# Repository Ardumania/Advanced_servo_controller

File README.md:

# Advanced_servo_controller
Based on ATtiny85 and PJON bus

In the last years I have worked in several projects related with education and robotics 
and I have found several problems, if you work with only one microcontroller you are very 
limited about the number of servos you can drive, you need a separate controller to 
drive until 32 servos, but it’s still possible. What about sensors? if you are planning 
to build an hexapod and mount two distance sensor for each leg It’s practically impossible.

There are systems for robotics that consist in smart servos connected by a RS-485 bus 
(Dynamixel or Ubtech), but in these systems is not possible to implement sensors on the 
same bus. And other problem is that those systems use a closed protocol and developers 
can’t implement their own sensors or actuators.

For several time I was thinking in an alternative system for implement sensors and actuators 
in a same communication bus and, of course, do it open allowing developers and enthusiast to 
design their own modules and share them. Initially thought in I2C bus be cause is well 
documented and easy to use but need 4 wires and there are no standard cable to use, this 
is an inconvenient.

In May 2015 I was talking in Valencia with my mentor and friend David Cuartielles about 
this project and he made me a suggestion: the PJON bus developed by an italian guy 
(Giovanni Blu), it’s one wire, addressable, fully bi-directional and open. That was 
instant love and this project could start.
PJON project can be found here: https://github.com/gioblu/PJON

The main goal of this project is to build a net of modules that can talk to each others
and with the main controller by only a one wire. Just think about it: one wire for data, 
one wire for GND and another wire for VCC, you can have a net of actuators and sensors 
just connected by standard servo wires… and can be connected up to 256 devices.

The first prototype is a servo module, actually called Advanced Servo Controller, and 
is in a very early state of development but it will work for sure be cause the concept 
is very simple: a small pcb with an ATtiny85 that communicates with a main controller 
(Arduino, of course) via a PJON bus, this ATtiny receives commands and generates the 
servo control signals. Commands can be like AT commands, e.g. “GT1500,2000”, this is 
Go To position 1500 in 2000 milliseconds, position is the servo control signal duty 
cycle in microseconds and final time is the time in which must reach that position 
from its actual position… simple. Each module has a current sensor a can send readings 
to the main controller as responses to a specific requests… and more capabilities can 
be implemented in the module firmware in the future.

In the future can be implemented more types of modules with sensors, e.g. distance sensors, 
which are very interesting in robotics.

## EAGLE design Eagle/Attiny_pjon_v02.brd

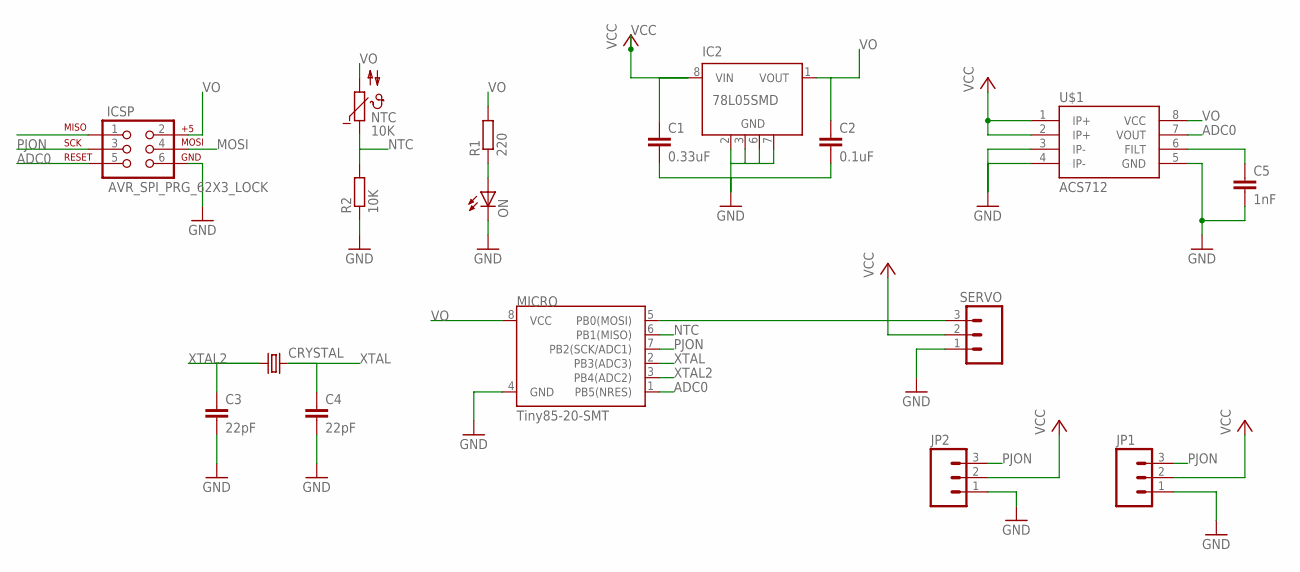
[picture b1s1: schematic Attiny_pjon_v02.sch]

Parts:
C1: 0.33uF; C1206
C2: 0.1uF; C1206
C3, C4: 22pF; C1206
C5: 1nF; C1206
CRYSTAL: CRYSTALSMD; HC49UP
IC2: 78L05SMD; SO08
ICSP: AVR_SPI_PRG_62X3_LOCK; 2X3_LOCK
JP1, JP2: M03PTH; 1X03
MICRO: Tiny85-20-SMT; SO08-EIAJ
NTC: 10K; P640
ON: LEDSMT1206; 1206
R1: 220; R1206
R2: 10K; R1206
SERVO: M03PTH; 1X03
U$1: ACS712; SO08

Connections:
ADC0: ICSP.5, MICRO.1 (PB5(NRES)), U$1.7 (VOUT)
GND: C1.2, C2.2, C3.2, C4.2, C5.2, IC2.2 (GND), IC2.3 (GND), IC2.6 (GND), IC2.7 (GND), ICSP.6, JP1.1, JP2.1, MICRO.4 (GND), ON.C, R2.1, SERVO.1, U$1.3 (IP-), U$1.4 (IP-), U$1.5 (GND)
MISO: ICSP.1
MOSI: ICSP.4, MICRO.5 (PB0(MOSI)), SERVO.3
unnamed: C5.1, U$1.6 (FILT)
unnamed: ON.A, R1.1
NTC: MICRO.6 (PB1(MISO)), NTC.1, R2.2
PJON: ICSP.3, JP1.3, JP2.3, MICRO.7 (PB2(SCK/ADC1))
VCC: C1.1, IC2.8 (VIN), JP1.2, JP2.2, SERVO.2, U$1.1 (IP+), U$1.2 (IP+)
VO: C2.1, IC2.1 (VOUT), ICSP.2, MICRO.8 (VCC), NTC.2, R1.2, U$1.8 (VCC)
XTAL: C4.1, CRYSTAL.2, MICRO.2 (PB3(ADC3))
XTAL2: C3.1, CRYSTAL.1, MICRO.3 (PB4(ADC2))

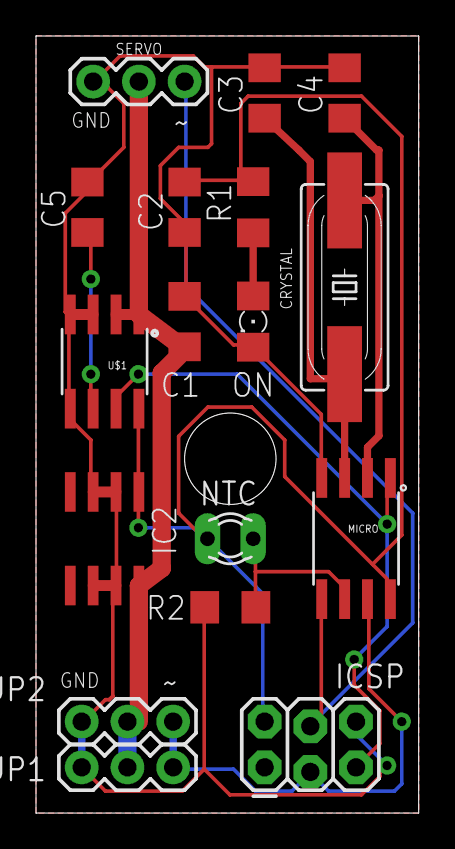
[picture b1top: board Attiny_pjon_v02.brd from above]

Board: 2 copper layers, 21.3 x 43.2 mm, 17 parts (0 on the bottom side), 11 nets.

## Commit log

2016-12-12 :space_invader: Added .gitattributes & .gitignore files
2016-12-12 Ver 0001
    Nothing of this works, it's only a prove of concept
2016-12-15 README.MD ver 0001
2016-12-15 ver 0002
2016-12-19 Folder name changed
2016-12-19 Actualización de README
2017-01-10 Board V0.2
    RGB LED Removed.
    Added external oscillator, temperature sensor and a center hole
2017-01-10 Comment recent changes in Eagle folder
2017-01-19 The project explained
    New version with more information about this madness
2017-01-19 The project explained
2017-01-20 Fixed some issues
2017-01-20 Added First version of the firmware
2017-02-23 Scheme V02
    Fixed an issue related with voltage regulator, tested in bread board
2017-02-23 Updated license
2017-02-23 Small program to save the id in a device
2017-02-23 Minos changes

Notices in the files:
parts and their libraries:
SparkFun-Connectors: Licensing: Creative Commons ShareAlike 4.0 International - https://creativecommons.org/licenses/by-sa/4.0
